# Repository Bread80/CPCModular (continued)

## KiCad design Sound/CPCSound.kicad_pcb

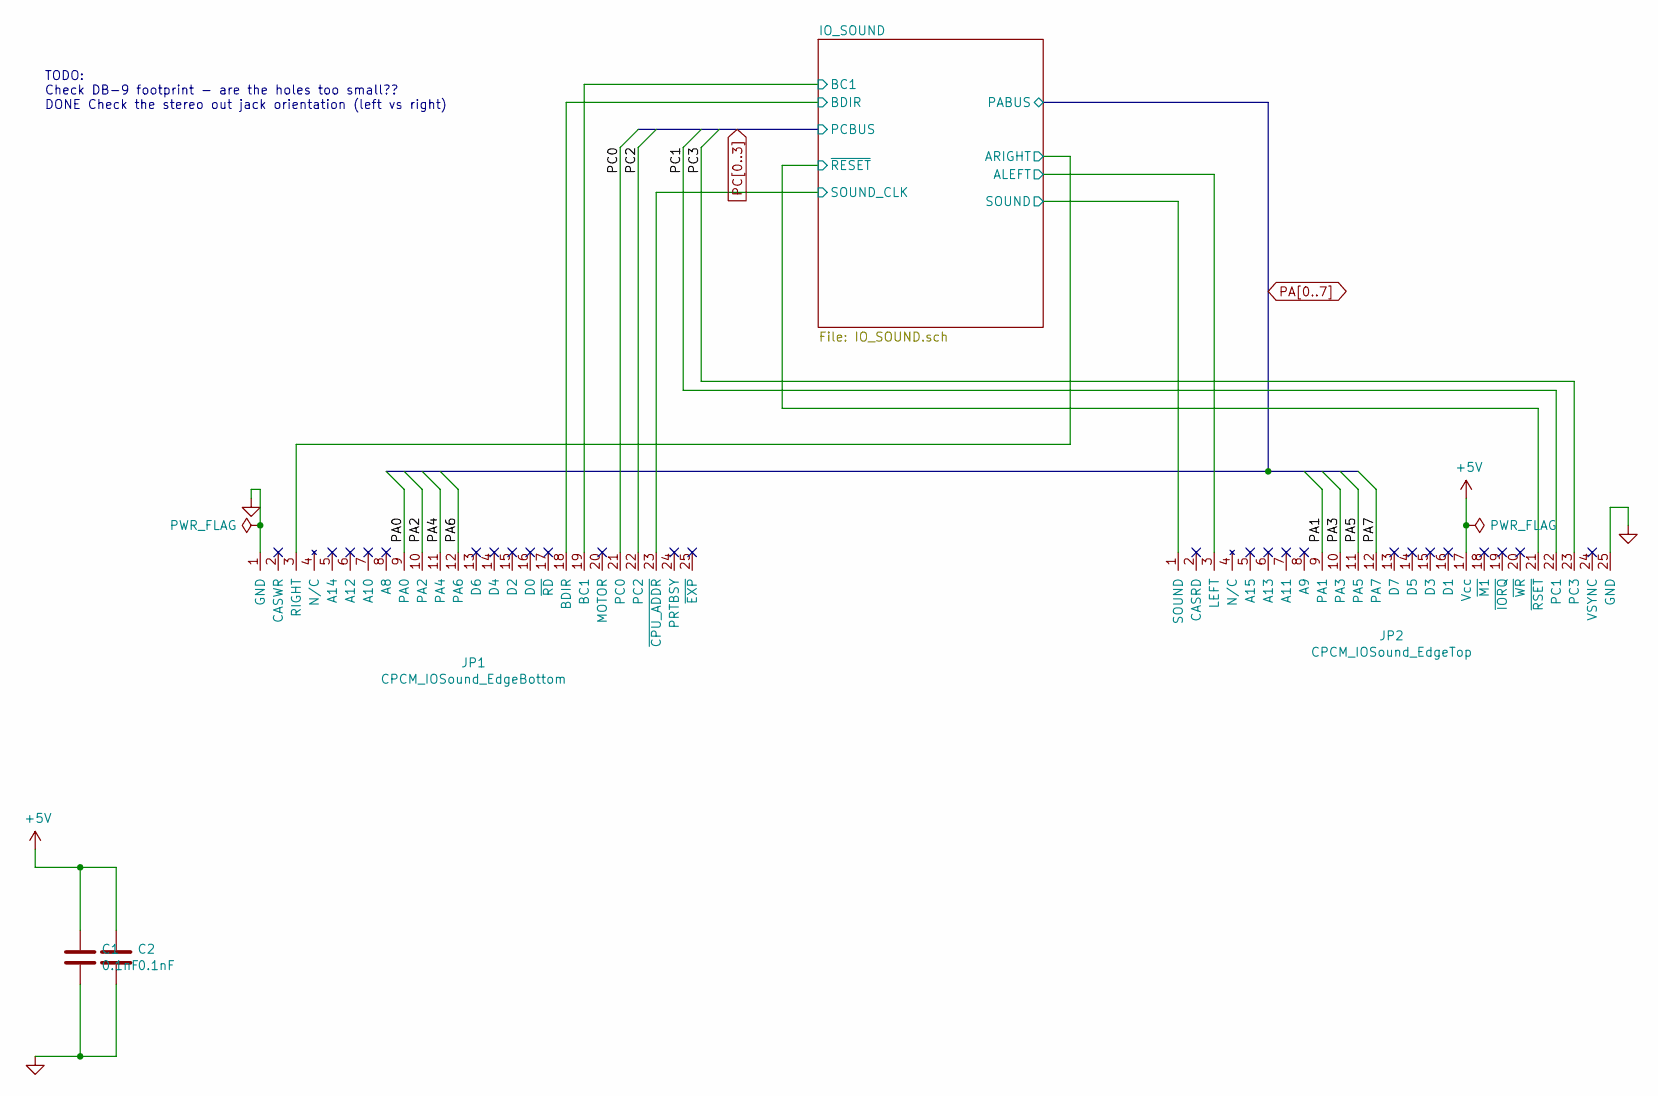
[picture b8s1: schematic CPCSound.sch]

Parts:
C1, C2: 0.1nF; C_Disc_D3.0mm_W2.0mm_P2.50mm
JP1: CPCM_IOSound_EdgeBottom; Edge25_2.54PS
JP2: CPCM_IOSound_EdgeTop; Edge25_2.54PS

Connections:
+5V: C1.1, C2.1, JP2.17 (Vcc); also elsewhere on the board
/IO_SOUND/ALEFT: JP2.3 (LEFT); also elsewhere on the board
/IO_SOUND/ARIGHT: JP1.3 (RIGHT); also elsewhere on the board
/IO_SOUND/BC1: JP1.19 (BC1); also elsewhere on the board
/IO_SOUND/BDIR: JP1.18 (BDIR); also elsewhere on the board
/IO_SOUND/SOUND: JP2.1 (SOUND); also elsewhere on the board
/IO_SOUND/SOUND_CLK: JP1.23 (~CPU_ADDR); also elsewhere on the board
/IO_SOUND/~RESET: JP2.21 (~RSET); also elsewhere on the board
GND: C1.2, C2.2, JP1.1 (GND), JP2.25 (GND); also elsewhere on the board
PA0: JP1.9 (PA0); also elsewhere on the board
PA1: JP2.9 (PA1); also elsewhere on the board
PA2: JP1.10 (PA2); also elsewhere on the board
PA3: JP2.10 (PA3); also elsewhere on the board
PA4: JP1.11 (PA4); also elsewhere on the board
PA5: JP2.11 (PA5); also elsewhere on the board
PA6: JP1.12 (PA6); also elsewhere on the board
PA7: JP2.12 (PA7); also elsewhere on the board
PC0: JP1.21 (PC0); also elsewhere on the board
PC1: JP2.22 (PC1); also elsewhere on the board
PC2: JP1.22 (PC2); also elsewhere on the board
PC3: JP2.23 (PC3); also elsewhere on the board

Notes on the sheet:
TODO: Check DB-9 footprint - are the holes too small?? DONE Check the stereo out jack orientation (left vs right)

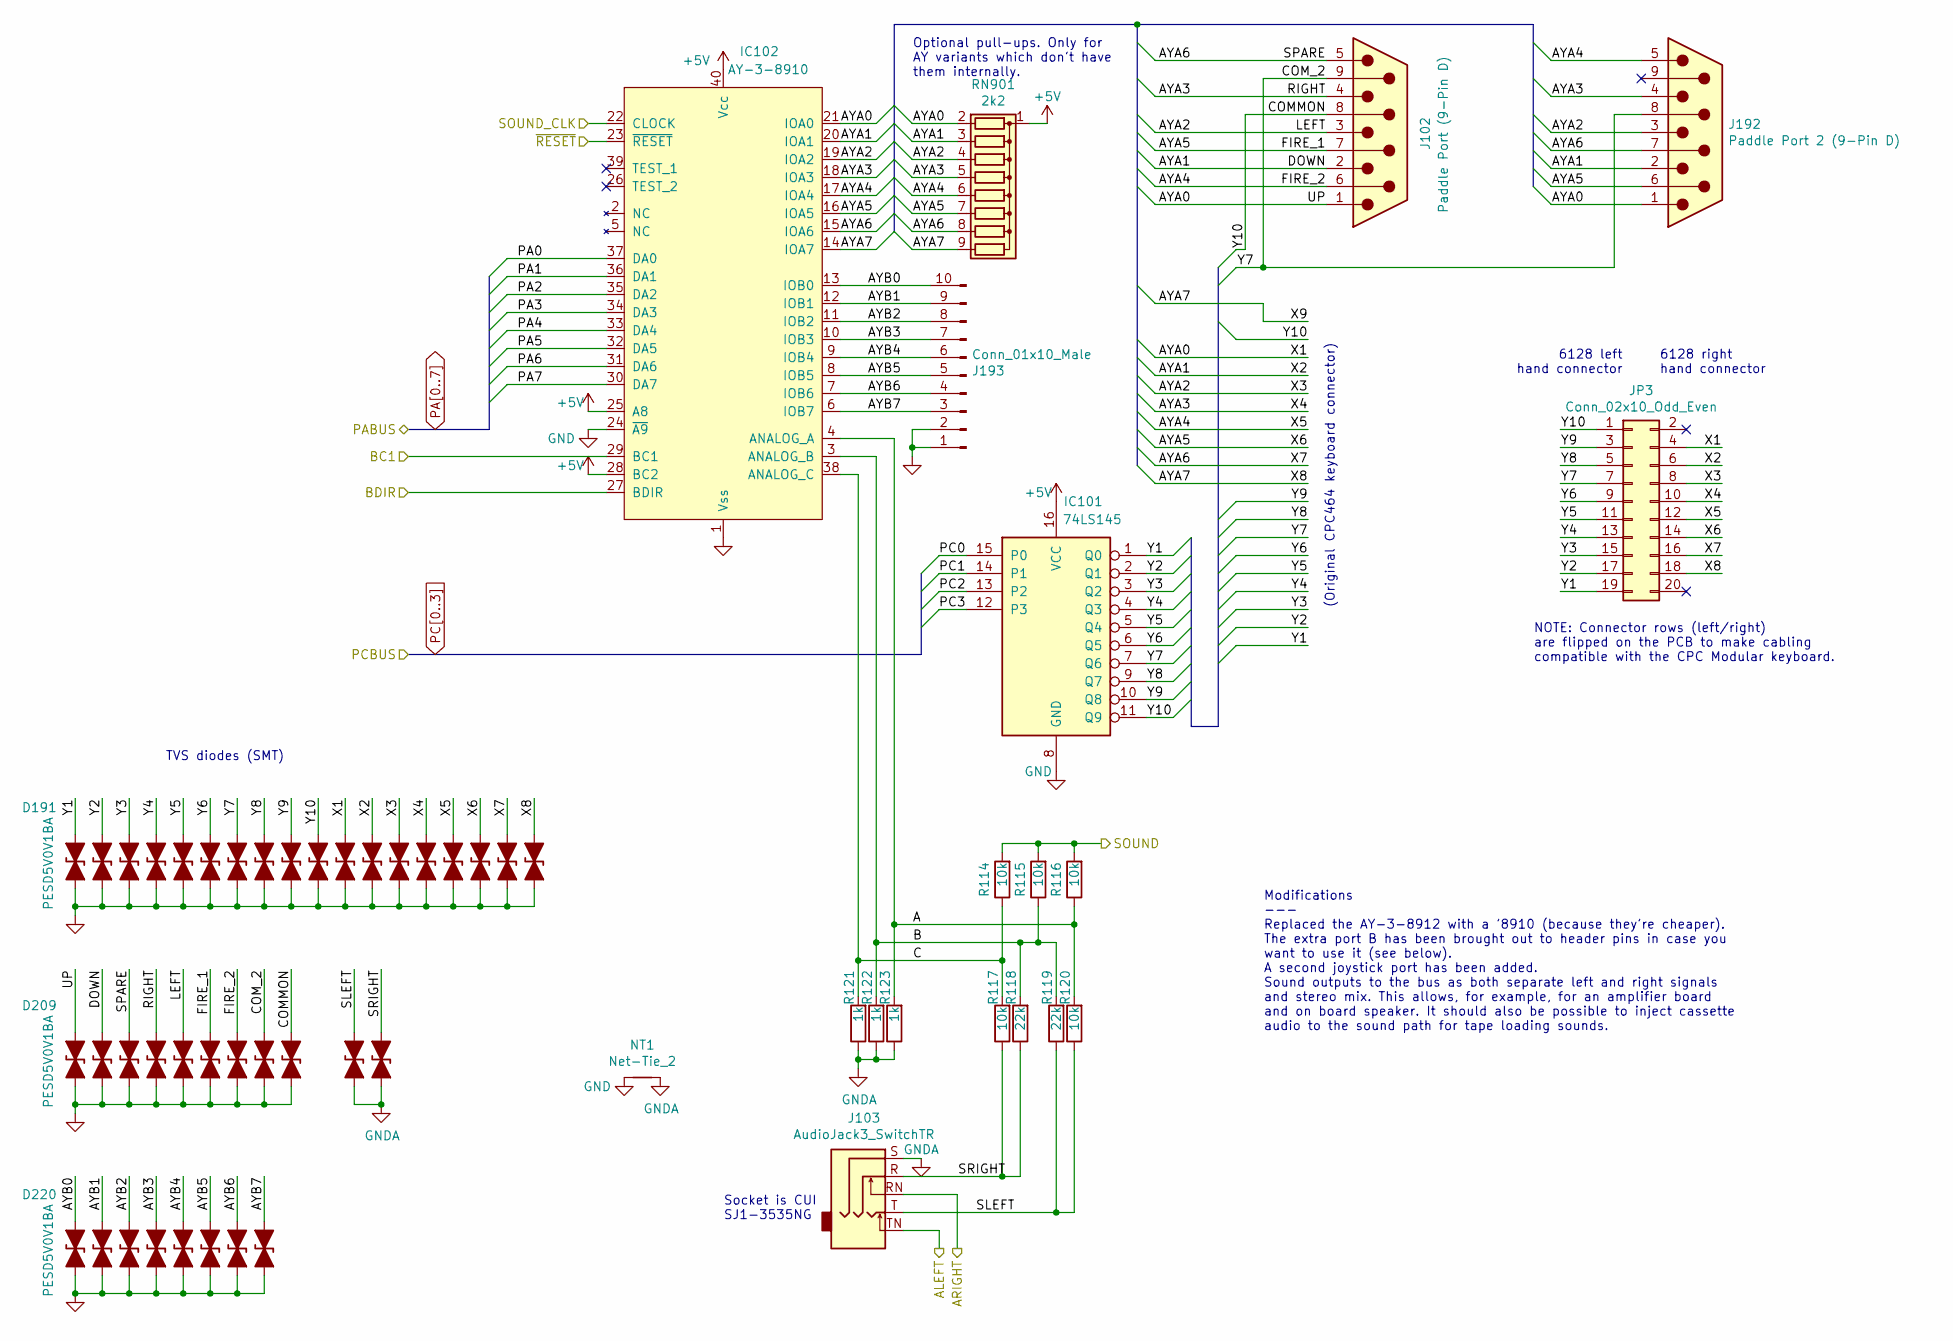
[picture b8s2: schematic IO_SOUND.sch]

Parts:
D191, D192, D193, D194, D195, D196, D197, D198, D199, D200, D201, D202, D203, D204, D205, D206, D207, D208, D209, D210, D211, D212, D213, D214, D215, D216, D217, D218, D219, D220, D221, D222, D223, D224, D225, D226, D227: PESD5V0V1BA; D_SOD-323_HandSoldering
IC101: 74LS145; DIP-16_W7.62mm_Socket
IC102: AY-3-8910; DIP-40_W15.24mm_Socket
J102: Paddle Port (9-Pin D); DSUB-9_Male_Horizontal_P2.77x2.84mm_EdgePinOffset9.90mm_Hou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
J103: AudioJack3_SwitchTR; Jack_3.5mm_CUI_SJ1-3535NG_Horizontal
J192: Paddle Port 2 (9-Pin D); DSUB-9_Male_Horizontal_P2.77x2.84mm_EdgePinOffset9.90mm_Hou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
J193: Conn_01x10_Male; PinHeader_2x05_P2.54mm_Vertical
JP3: Conn_02x10_Odd_Even; IDC-Header_2x10_P2.54mm_Vertical
NT1: Net-Tie_2; NetTie-2_SMD_Pad0.5mm
R114, R115, R116, R117, R120: 10k; R_Axial_DIN0207_L6.3mm_D2.5mm_P7.62mm_Horizontal
R118, R119: 22k; R_Axial_DIN0207_L6.3mm_D2.5mm_P7.62mm_Horizontal
R121, R122, R123: 1k; R_Axial_DIN0207_L6.3mm_D2.5mm_P7.62mm_Horizontal
RN901: 2k2; R_Array_SIP9

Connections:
+5V: IC101.16 (VCC), IC102.25 (A8), IC102.28 (BC2), IC102.40 (Vcc), RN901.1 (common); also elsewhere on the board
/IO_SOUND/A: IC102.4 (ANALOG_A), R116.1, R120.2, R123.2
/IO_SOUND/ALEFT: J103.TN; also elsewhere on the board
/IO_SOUND/ARIGHT: J103.RN; also elsewhere on the board
/IO_SOUND/AYA0: D201.1 (A1), D209.1 (A1), IC102.21 (IOA0), J102.1, J192.1, JP3.4, RN901.2 (R1)
/IO_SOUND/AYA1: D202.1 (A1), D210.1 (A1), IC102.20 (IOA1), J102.2, J192.2, JP3.6, RN901.3 (R2)
/IO_SOUND/AYA2: D203.1 (A1), D213.1 (A1), IC102.19 (IOA2), J102.3, J192.3, JP3.8, RN901.4 (R3)
/IO_SOUND/AYA3: D204.1 (A1), D212.1 (A1), IC102.18 (IOA3), J102.4, J192.4, JP3.10, RN901.5 (R4)
/IO_SOUND/AYA4: D205.1 (A1), D215.1 (A1), IC102.17 (IOA4), J102.6, J192.5, JP3.12, RN901.6 (R5)
/IO_SOUND/AYA5: D206.1 (A1), D214.1 (A1), IC102.16 (IOA5), J102.7, J192.6, JP3.14, RN901.7 (R6)
/IO_SOUND/AYA6: D207.1 (A1), D211.1 (A1), IC102.15 (IOA6), J102.5, J192.7, JP3.16, RN901.8 (R7)
/IO_SOUND/AYA7: D208.1 (A1), IC102.14 (IOA7), JP3.18, RN901.9 (R8)
/IO_SOUND/AYB0: D220.1 (A1), IC102.13 (IOB0), J193.10
/IO_SOUND/AYB1: D221.1 (A1), IC102.12 (IOB1), J193.9
/IO_SOUND/AYB2: D222.1 (A1), IC102.11 (IOB2), J193.8
/IO_SOUND/AYB3: D223.1 (A1), IC102.10 (IOB3), J193.7
/IO_SOUND/AYB4: D224.1 (A1), IC102.9 (IOB4), J193.6
/IO_SOUND/AYB5: D225.1 (A1), IC102.8 (IOB5), J193.5
/IO_SOUND/AYB6: D226.1 (A1), IC102.7 (IOB6), J193.4
/IO_SOUND/AYB7: D227.1 (A1), IC102.6 (IOB7), J193.3
/IO_SOUND/B: IC102.3 (ANALOG_B), R115.1, R118.2, R119.2, R122.2
/IO_SOUND/BC1: IC102.29 (BC1); also elsewhere on the board
/IO_SOUND/BDIR: IC102.27 (BDIR); also elsewhere on the board
/IO_SOUND/C: IC102.38 (ANALOG_C), R114.1, R117.2, R121.2
/IO_SOUND/COMMON: D200.1 (A1), D217.1 (A1), IC101.11 (Q9), J102.8, JP3.1
/IO_SOUND/COM_2: D197.1 (A1), D216.1 (A1), IC101.7 (Q6), J102.9, J192.8, JP3.7
/IO_SOUND/SLEFT: D218.1 (A1), J103.T, R119.1, R120.1
/IO_SOUND/SOUND: R114.2, R115.2, R116.2; also elsewhere on the board
/IO_SOUND/SOUND_CLK: IC102.22 (CLOCK); also elsewhere on the board
/IO_SOUND/SRIGHT: D219.1 (A1), J103.R, R117.1, R118.1
/IO_SOUND/Y1: D191.1 (A1), IC101.1 (Q0), JP3.19
/IO_SOUND/Y2: D192.1 (A1), IC101.2 (Q1), JP3.17
/IO_SOUND/Y3: D193.1 (A1), IC101.3 (Q2), JP3.15
/IO_SOUND/Y4: D194.1 (A1), IC101.4 (Q3), JP3.13
/IO_SOUND/Y5: D195.1 (A1), IC101.5 (Q4), JP3.11
/IO_SOUND/Y6: D196.1 (A1), IC101.6 (Q5), JP3.9
/IO_SOUND/Y8: D198.1 (A1), IC101.9 (Q7), JP3.5
/IO_SOUND/Y9: D199.1 (A1), IC101.10 (Q8), JP3.3
/IO_SOUND/~RESET: IC102.23 (~RESET); also elsewhere on the board
GND: D191.2 (A2), D192.2 (A2), D193.2 (A2), D194.2 (A2), D195.2 (A2), D196.2 (A2), D197.2 (A2), D198.2 (A2), D199.2 (A2), D200.2 (A2), D201.2 (A2), D202.2 (A2), D203.2 (A2), D204.2 (A2), D205.2 (A2), D206.2 (A2), D207.2 (A2), D208.2 (A2), D209.2 (A2), D210.2 (A2), D211.2 (A2), D212.2 (A2), D213.2 (A2), D214.2 (A2), D215.2 (A2), D216.2 (A2), D217.2 (A2), D220.2 (A2), D221.2 (A2), D222.2 (A2), D223.2 (A2), D224.2 (A2), D225.2 (A2), D226.2 (A2), D227.2 (A2), IC101.8 (GND), IC102.1 (Vss), IC102.24 (~A9), J193.1, J193.2, NT1.1; also elsewhere on the board
GNDA: D218.2 (A2), D219.2 (A2), J103.S, NT1.2, R121.1, R122.1, R123.1
PA0: IC102.37 (DA0); also elsewhere on the board
PA1: IC102.36 (DA1); also elsewhere on the board
PA2: IC102.35 (DA2); also elsewhere on the board
PA3: IC102.34 (DA3); also elsewhere on the board
PA4: IC102.33 (DA4); also elsewhere on the board
PA5: IC102.32 (DA5); also elsewhere on the board
PA6: IC102.31 (DA6); also elsewhere on the board
PA7: IC102.30 (DA7); also elsewhere on the board
PC0: IC101.15 (P0); also elsewhere on the board
PC1: IC101.14 (P1); also elsewhere on the board
PC2: IC101.13 (P2); also elsewhere on the board
PC3: IC101.12 (P3); also elsewhere on the board

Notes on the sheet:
Modifications --- Replaced the AY-3-8912 with a '8910 (because they're cheaper). The extra port B has been brought out to header pins in case you want to use it (see below). A second joystick port has been added. Sound outputs to the bus as both separate left and right signals and stereo mix. This 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
Socket is CUI SJ1-3535NG
6128 left hand connector
6128 right hand connector
Optional pull-ups. Only for AY variants which don't have them internally.
(Original CPC464 keyboard connector)
NOTE: Connector rows (left/right) are flipped on the PCB to make cabling compatible with the CPC Modular keyboard.
TVS diodes (SMT)

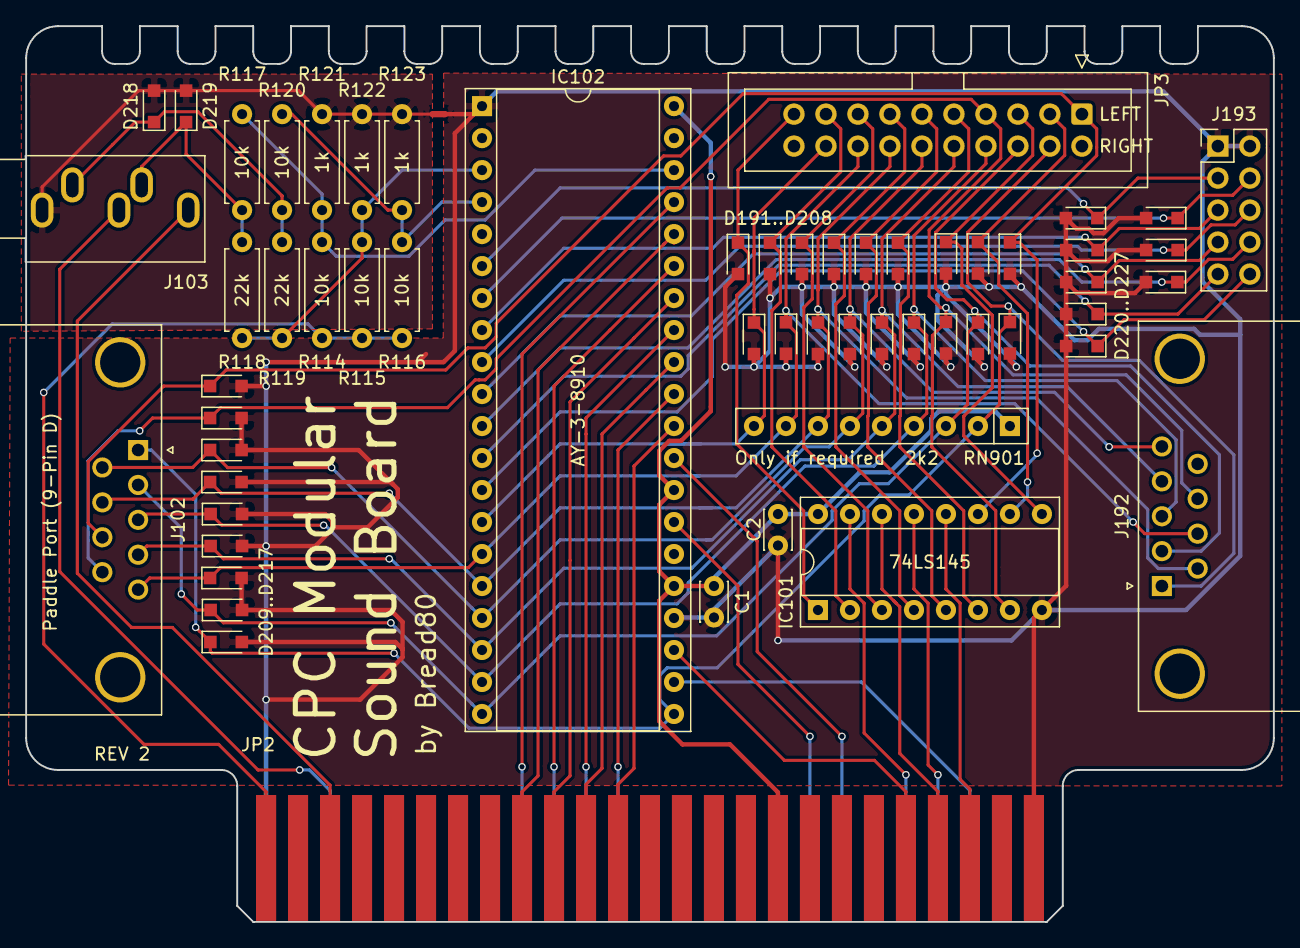
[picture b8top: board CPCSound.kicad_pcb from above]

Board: 2 copper layers, 99.1 x 71.1 mm, 60 parts (1 on the bottom side), 53 nets.

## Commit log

2023-09-27 Update licence and readme
2023-09-29 Added image to readme
2023-09-29 Tidying readme
2023-09-29 More readme tidying
2023-09-29 Even more readme tidying
2025-03-29 Long overdue update...
